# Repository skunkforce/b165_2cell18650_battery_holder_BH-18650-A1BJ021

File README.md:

# edgy_board number b165
This design is part of the [edgy board project](https://github.com/skunkforce/edgy_boards).

# getting started
This repository uses submodules. After cloning use the command 

```$ git submodule update --init --recursive```

to pull the submodules before opening the project with kicad. 

# Tests
Tests can be found in [TESTS.md](TESTS.md)

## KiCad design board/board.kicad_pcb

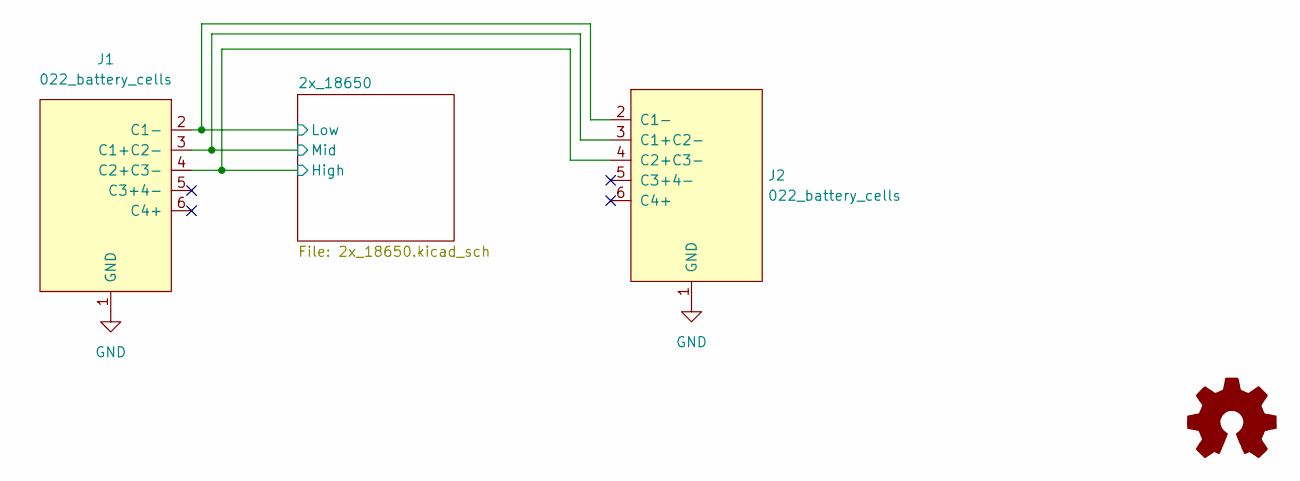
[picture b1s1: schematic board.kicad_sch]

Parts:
J1: 022_battery_cells; on_edge_2x05_device
J2: 022_battery_cells; on_edge_2x05_host
LOGO1: Logo_Open_Hardware_Small; OSHW-Symbol_6.7x6mm_SilkScreen

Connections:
/2x_aaa/High: J1.4 (C2+C3-), J2.4 (C2+C3-); also elsewhere on the board
/2x_aaa/Low: J1.2 (C1-), J2.2 (C1-); also elsewhere on the board
/2x_aaa/Mid: J1.3 (C1+C2-), J2.3 (C1+C2-); also elsewhere on the board
GND: J1.1 (GND), J2.1 (GND)

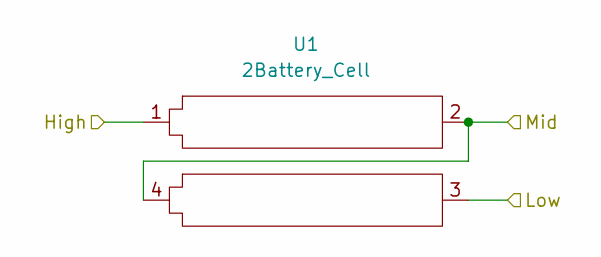
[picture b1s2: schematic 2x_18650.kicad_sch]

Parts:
U1: 2Battery_Cell; 2_18650_cell_holder; lcsc C20606804

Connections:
/2x_aaa/High: U1.1; also elsewhere on the board
/2x_aaa/Low: U1.3; also elsewhere on the board
/2x_aaa/Mid: U1.2, U1.4; also elsewhere on the board

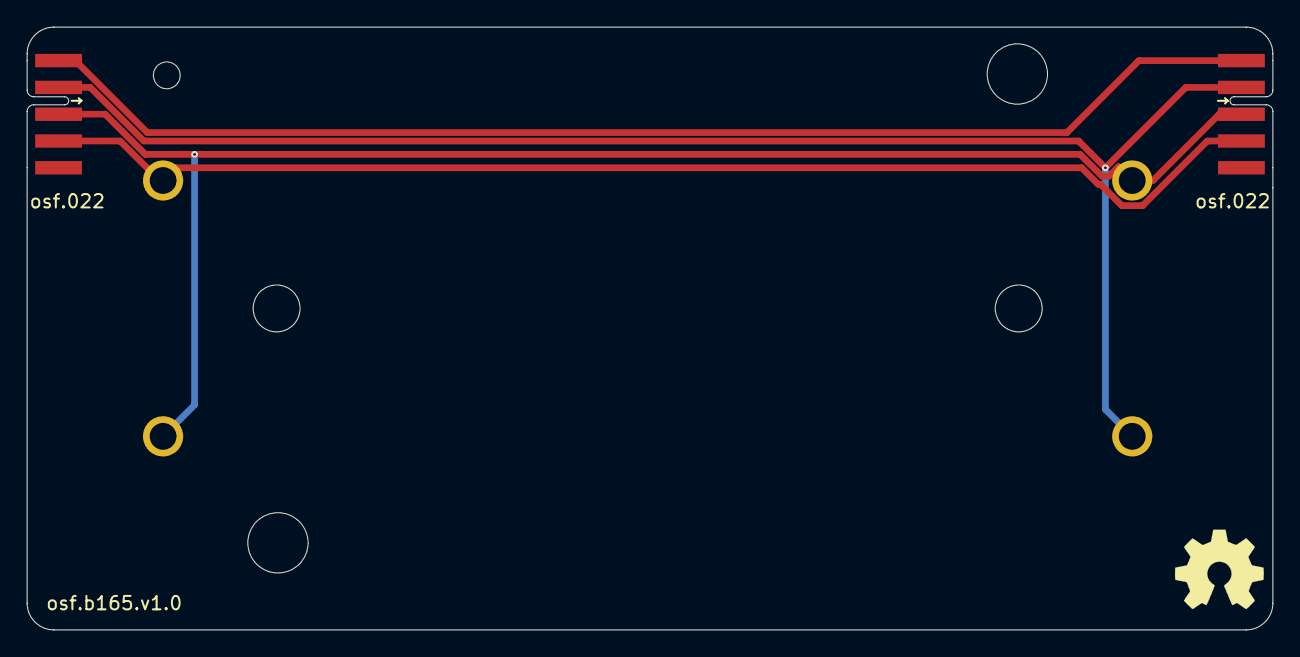
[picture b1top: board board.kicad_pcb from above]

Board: 2 copper layers, 93.0 x 45.0 mm, 4 parts (0 on the bottom side), 4 nets.

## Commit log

2023-04-04 initial
2023-04-04 added custom footprint
2023-05-03 added render
2023-05-25 added silkscreen + and - so that the pattery polarization is clear. added resistor for connection to GND if needed
2024-03-07 improved hole geometry
2025-04-13 changed to 18650 holder
